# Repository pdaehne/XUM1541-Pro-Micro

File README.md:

# XUM1541 Pro Micro

The XUM1541 allows to connect devices that use the Commodore serial bus (IEC
bus) to modern computers via USB. You usually use it to create images of old
1541 or 1571 floppy disks by using a software called
[OpenCBM](https://github.com/OpenCBM/OpenCBM).

## Acknowlegements

This device is a clone of the
[ZoomFloppy](https://www.go4retro.com/products/zoomfloppy/) device developed by
Nate Lawson. It does not have the IEEE-488 interface, but apart from that it has
the same circuit as documented in the file
[zoomfloppy-schem-20100704.png](https://github.com/OpenCBM/OpenCBM/blob/master/xum1541/zoomfloppy-schem-20100704.png)
in the OpenCBM repository.

The idea for the "Activity" LED was taken from the
[XUM1541-II](https://github.com/tebl/C64-XUM1541-II) device designed by tebl.

## Ordering the PCB

The subdirectory "gerber-files" contains a Zip file you can use to order the PCB
from PCB manufacturers like PCBWay or JLCPCB. Simply upload the Zip on their web
page. When you plan to use the parallel port option, you have to order a PCB
that has the default thickness of 1.6mm, and I recommend to order a surface
finish of ENIG with gold fingers and chamfered edges, because it is much more
durable than the default HASL finish.

## Building the Adapter

### Bill of Materials

* __1x Pro Micro ATmega32U4 5V 16MHz Board__.

  There are two variants of this board, a 5V variant with 16MHz clock
  frequency, and a 3V variant with 8MHz. Make sure that you get the 5V variant!
  Also make sure that you get a Pro Micro Board based on the ATmega32U4. There
  are Pro Micro Boards available based on the Raspberry Pi Pico, these do not
  work!

  These boards come in at least three different widths. This XUM1541 PCB is
  designed to support all three widths (the distance between the two rows of
  pins can be either 15.24mm, 17.78mm or 20.32mm).

* __2x 1x12 Pin Headers Through Hole Straight 2.54mm pitch__

  These go onto the Pro Micro board. They should be included with the Pro Micro
  board.

* (Optional) __2x 2x12 Pin Sockets Through Hole Straight 2.54mm pitch__.

  These are used to connect the Pro Micro Board to the XUM1541 PCB. They are
  optional, you can solder the Pro Micro directly to the PCB instead.

* __1x 6 Pin DIN Socket Right Angle PCB mount__.

  The footprint is for Lumberg 010599 06 or equivalent sockets.

* (Optional) __1x 74LS06 Hex Inverter Buffers DIL-14__ (U1).

  Using this buffer chip is strongly recommended, especially when your're
  daisychaining more than one device on the IEC bus, but it is optional. When
  you install it, you should also install the capacitor C1 and the resistor
  network RN2. When you do not install it, you have to close the corresponding
  5 solder jumpers on the bottom of the XUM1541 PCB.

* (Optional) __1x IC Socket DIL-14__ (U1).

  Socket for the 74LS06. It is optional, you can alternatively solder the IC
  directly onto the XUM1541 PCB.

* (Optional) __1x Ceramic Capacitor 100nF 2.5mm pitch__ (C1).

  This is the blocking capacitor for U1. It is optional, you only need to
  install it when you install the 74LS06.

* (Optional) __1x Resistor Network 5x100kOhm SIL-6 Star Connection__ (RN2).

  This resistor network is only needed when installing the 74LS06. It pulls the
  inputs of the 74LS06 to ground.

  Warning: Please make sure that you get the right kind of resistor network.
  This network consists of 5 resistors which share one common connection on one
  side, i.e. there are 5 + 1 = 6 pins.

* (Optional) __1x Resistor Network 5x4.7kOhm SIL-10 Single Resistors__ (RN1).

  This resistor network is not used when you do not install the 74LS06.
  
  When you do install the 74LS06, you may optionally install this resistor
  network to limit the amount of current on the IEC bus. When you install the
  74LS06 and decide to leave this resistor network unpopulated, you have to
  close the corresponding 5 solder jumpers on the bottom of the XUM1541 PCB.

  Warning: Please make sure that you get the right kind of resistor network.
  This network consists of 5 resistors which all have their own separate two
  connections, i.e. there are 5 x 2 = 10 pins.

* (Optional) __1x Push Button 6x6mm__ (SW1).

  A reset switch that resets the Pro Micro, i.e. puts it into bootloader mode
  for 8 seconds. Completely optional, but having this switch makes installing
  a new firmware much more simple.

* (Optional) __2x LEDs 3mm or 5mm__ (D1 and D2).

  These are the power and activity LEDs. You can use any color you want, e.g.
  red for power and green for activity. These LEDs are optional, there are
  already corresponding LEDs on the Pro Micro board. When you install them, you
  also have to install matching series resistors R1 and R2. The activity LED
  requires an installed 74LS06!

* (Optional) __2x Resistors size 0207__ (R1 and R2).

  These are the series resistors for the LEDs D1 and D2. Of course they are only
  required when you actually install these LEDs! Their value depends on the
  types of LEDs you use (color) as well as the brightness you want to get. I
  recommend that you use a breadboard and check which values are ok for you.

* (Optional) __1x 1x3 Pin Headers Through Hole Straight 2.54mm pitch__

  This is a header for a serial TTL connection to the ATmega. This is only
  needed when you want to debug the XUM1541 firmware running on the
  microcontroller. You will probably not need this header. When you use it,
  keep in mind that it uses two pins also used by the parallel port of the
  XUM1541, so you will not be able to use both simultaneously.

### Soldering the Pin Headers to the Pro Micro Board

The first step is to solder the two 1x12 pin headers to the Pro Micro board.
I recommend to use a breadboard to make sure that the pin headers are correctly
aligned. But be careful not to drop solder onto the breadboard!

### Soldering the Socket for U1 (74LS06), the Capacitor C1 and the Resistor Networks RN2 and RN1

There are three options for building the XUM1541:

1. The simple version without U1, C1, RN2 and RN1. I generally do not recommend
   this option. You should only connect one single device to the IEC bus when
   using this option. You have to close the five solder jumpers below the U1
   footprint on the bottom of the PCB, and that is all.

2. The version with U1, C1 and RN2, but without RN1. The 74LS06 on U1 is a
   buffer chip, i.e. it is used to amplify the signals of the Pro Micro and to
   protect the ports of the Pro Micro. It is strongly recommended to install U1
   when you plan to connect more than one device to the IEC bus. RN2 are
   pull-down resistors to force the inputs of U1 to GND level when not driven by
   the Pro Micro.

   You can either install a DIL-14 socket for U1, or you can directly solder the
   74LS06 IC to the XUM1541 PCB. I personally prefer to use sockets. Make sure
   that the little notch of the socket points to the direction marked on the
   silk screen (to the right on the photo below).

   I recommend to wait until you are finished with soldering before you install
   the 74LS06 into the socket. Again make sure that the notch of the IC points
   to the direction of the notch of the socket (to the right on the photo).

   Now you have to install the blocking capacitor C1 next to U1.

   And you have to install the resistor network RN2 next to U1. Be careful, the
   orientation of this resistor network matters! There is a small dot on the
   resistor network that marks pin 1. Pin 1 is also marked on the silk screen
   of the PCB (left on the picture below).

   Because you are not installing resistor network RN1, you have to close five
   solder jumpers on the bottom of the PCB.

3. The full version with U1, C1, RN2 and RN1. This is the recommended version.
   RN1 limits the current between the IEC bus and the Pro Micro and protects the
   ports of the Pro Micro as well as your valuable retro devices connected to
   the IEC bus. The electric circuit is exactly the same as used for the
   [ZoomFloppy](https://www.go4retro.com/products/zoomfloppy/) available for
   purchase from Retro Innovations.

   Additionally to installing U1, C1 and RN2 (see documentation for variant 2
   above), you have to install resistor network RN1. Unlike resistor network
   RN2, the orientation of the network does not matter, but it is nevertheless
   good practice to solder pin 1 with the dot into the hole marked on the silk
   screen (at the top in the picture below).

### Soldering the Pin Sockets for the Pro Micro Board

This step is completely optional. You can solder the Pro Micro board directly
onto the XUM1541 PCB, but I prefer to install Pin Sockets.

There are two rows of through-holes on the PCB for each side of the Pro Micro
board. Each pair of rows has the same electrical connections, so you can freely
choose which one to use to adjust to different widths of the Pro Micro. When
the distance of the two rows of pins of your Pro Micro is 15.24mm, use the two
inner rows. When the distance is 20.32mm, use the two outer rows. When the
distance is 17.78mm, you use the outer row on one side, and the inner row on the
other side.

To solder the pin sockets straight, I recommend to stick them onto the pin
headers of the Pro Micro and put them onto the PCB. But again, be careful not
to drop solder onto the Pro Micro!

### Soldering the 6 Pin DIN socket

Now solder the 6 pin DIN socket onto the XUM1541 PCB. This is a straightforward
task.

### Soldering the Debug Header

The 1x3 pin header for debugging is optional. It provides a serial interface
with TTL levels and might be helpful when you are making changes to the firmware
of the Pro Micro, because you can use a serial terminal on another computer to
receive debug output from the Pro Micro.

### Soldering the LEDs and their series resistors

The LEDs for activity and power as well as their respective series resistors are
also optional. There are already corresponding LEDs on the Pro Micro board. I
intentionally do not give any values for the resistors here, because they depend
on the type of LED (color) you use as well as the level of brightness you want
to get. I recommend that you test different resistor values on a breadboard to
determine the right resistor values.

Important: The activity LED requires U1 to be installed!

When soldering the LEDs, keep in mind that the orientation of the LED matters.
There is a side of the LEDs that is flattened. This side is also marked on the
silk screen (the side facing away from the resistors). Unfortunately, this might
be little bit hard to see. Another hint is the length of the LED leads - the
long lead is the anode (+) and goes to the resistors, the short lead is the
cathode (-) and must point away from the resistors.

### Soldering the Reset Button

The reset button SW1 is optional. Pressing the reset button switches the Pro
Micro into boot loader mode for 8 seconds. Having a dedicated reset switch makes
installing a new firmware on the ATmega32U4 much simpler.

## Installing the Firmware

After soldering the XUM1541, you have to install the firmware onto the
Pro Micro. You will find the precompiled firmware in the
[OpenCBM GitHub repository](https://github.com/OpenCBM/OpenCBM/tree/master/xum1541).
Make sure that you fetch the correct firmware:

* When you did not install U1 (74LS06), you have to install the firmware
  "xum1541-PROMICRO-v??.hex", where "??" is the version number.

* When you did install U1, you have to install the firmware
  "xum1541-PROMICRO_7406-v??.hex".

There are many different ways to install the firmware. You can use an Atmel ICSP
programmer (or another Arduino), or you can install the firmware via the USB
port. The Pro Micro usually comes with the Arduino Leonardo boot loader
pre-installed. You switch the Pro Micro into boot loader mode by pressing the
reset button. When you did not install the reset button, you have to short the
RST pin of the Pro Micro board to GND. The Pro Micro stays in boot loader mode
for only 8 seconds, so you have to be quick now! I used a software called
"[avrdude](https://github.com/avrdudes/avrdude)" to install the firmware.
avrdude is also used by the Arduino IDE, so a simple way to get avrdude is to
install the Arduino IDE. I used the following command line to install the
firmware:

```
avrdude -v -patmega32u4 -cavr109 "-P/dev/tty.usbmodem2101" -b57600 -D "-Uflash:w:xum1541-PROMICRO_7406-v08.hex:i"
```

Of course you have to adjust the command line, especially the serial port!

## Installing OpenCBM

For installing OpenCBM, I recommend to have a look into the official
"[OpenCBM Users Guide](https://opencbm.trikaliotis.net/)" for more
information.

## Using a Parallel Cable

When you have a 1541 with a parallel cable, you can use that cable to achieve
much higher transfer rates. Simply connect the userport connector that you
usually connect to your C64 to the "Userport" at the side of the XUM1541. You
do not need to install any special kernal in your floppy - OpenCBM automatically
detects the presence of the cable and installs all necessary software on the
floppy. It should work out of the box.

When do not yet have a parallel cable, you might be interested in the following
of my projects:

https://github.com/pdaehne/C64-Parallel-Floppy-Cable

## License

XUM1541 Pro Micro (c) by Patrick Dähne

XUM1541 Pro Micro is licensed under a
Creative Commons Attribution-NonCommercial-ShareAlike 4.0 International License.

You should have received a copy of the license along with this
work. If not, see <https://creativecommons.org/licenses/by-nc-sa/4.0/>.

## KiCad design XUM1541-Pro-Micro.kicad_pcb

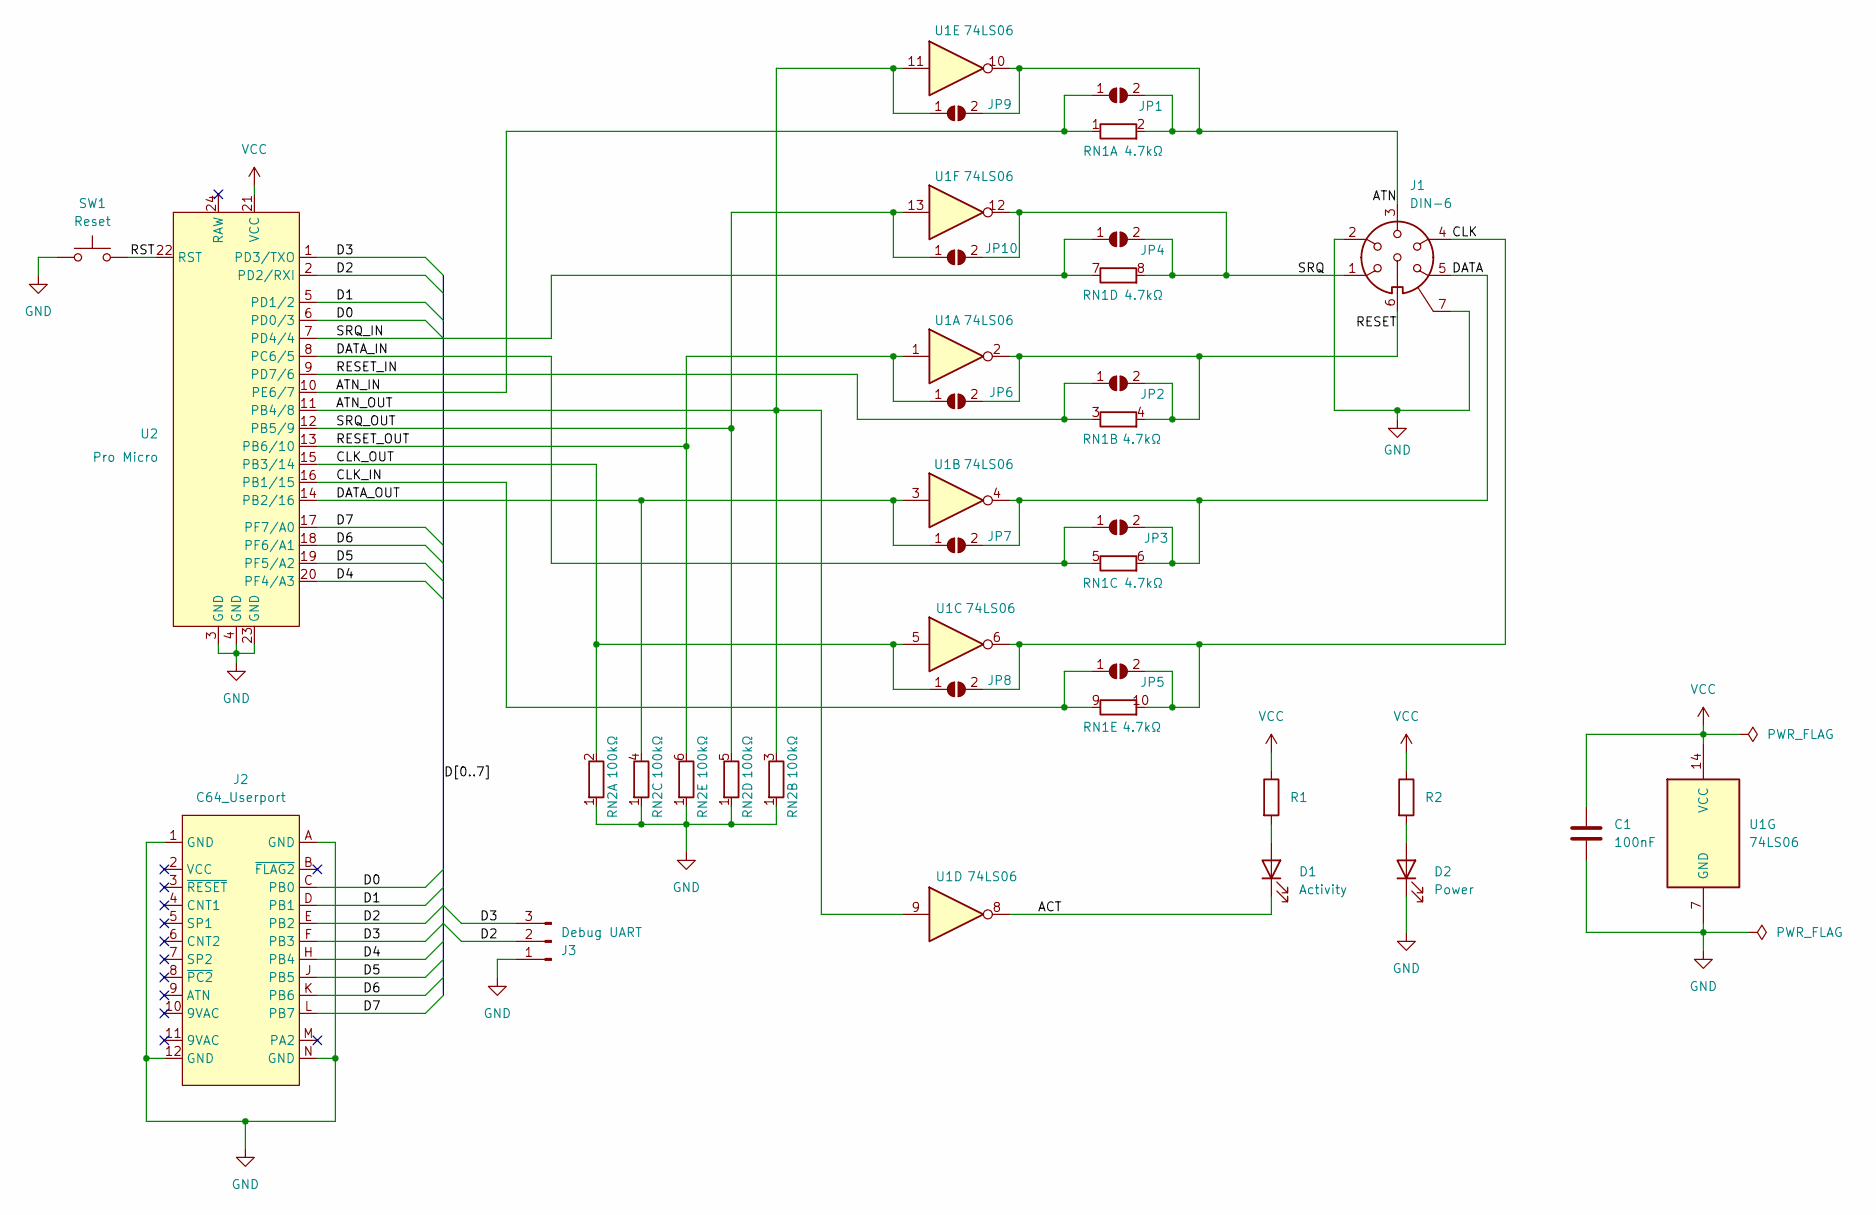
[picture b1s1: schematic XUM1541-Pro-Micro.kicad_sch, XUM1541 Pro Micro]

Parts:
C1: 100nF; C_Disc_D3.0mm_W1.6mm_P2.50mm
D1: Activity; LED_D3.0mm
D2: Power; LED_D3.0mm
J1: DIN-6
J2: C64_Userport; C64_Userport_Edge
J3: Debug UART; PinHeader_1x03_P2.54mm_Vertical
JP1, JP2, JP3, JP4, JP5, JP6, JP7, JP8, JP9, JP10: SolderJumper_2_Open; SolderJumper-2_P1.3mm_Open_RoundedPad1.0x1.5mm
R1, R2: R; R_Axial_DIN0207_L6.3mm_D2.5mm_P10.16mm_Horizontal
RN1: 4.7kΩ; R_Array_SIP10
RN2: 100kΩ; R_Array_SIP6
SW1: Reset; SW_PUSH_6mm
U1: 74LS06; DIP-14_W7.62mm_Socket_LongPads
U2: Pro Micro; Pro_Micro

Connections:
/ACT: D1.1 (K), U1.8
/ATN: J1.3, JP1.2 (B), JP9.2 (B), RN1.2 (R1.2), U1.10
/ATN_IN: JP1.1 (A), RN1.1 (R1.1), U2.10 (PE6/7)
/ATN_OUT: JP9.1 (A), RN2.3 (R2.2), U1.9, U1.11, U2.11 (PB4/8)
/CLK: J1.4, JP5.2 (B), JP8.2 (B), RN1.10 (R5.2), U1.6
/CLK_IN: JP5.1 (A), RN1.9 (R5.1), U2.16 (PB1/15)
/CLK_OUT: JP8.1 (A), RN2.2 (R1.2), U1.5, U2.15 (PB3/14)
/D0: J2.C (PB0), U2.6 (PD0/3)
/D1: J2.D (PB1), U2.5 (PD1/2)
/D2: J2.E (PB2), J3.2, U2.2 (PD2/RXI)
/D3: J2.F (PB3), J3.3, U2.1 (PD3/TXO)
/D4: J2.H (PB4), U2.20 (PF4/A3)
/D5: J2.J (PB5), U2.19 (PF5/A2)
/D6: J2.K (PB6), U2.18 (PF6/A1)
/D7: J2.L (PB7), U2.17 (PF7/A0)
/DATA: J1.5, JP3.2 (B), JP7.2 (B), RN1.6 (R3.2), U1.4
/DATA_IN: JP3.1 (A), RN1.5 (R3.1), U2.8 (PC6/5)
/DATA_OUT: JP7.1 (A), RN2.4 (R3.2), U1.3, U2.14 (PB2/16)
/RESET: J1.6, JP2.2 (B), JP6.2 (B), RN1.4 (R2.2), U1.2
/RESET_IN: JP2.1 (A), RN1.3 (R2.1), U2.9 (PD7/6)
/RESET_OUT: JP6.1 (A), RN2.6 (R5.2), U1.1, U2.13 (PB6/10)
/RST: SW1.2, U2.22 (RST)
/SRQ: J1.1, JP4.2 (B), JP10.2 (B), RN1.8 (R4.2), U1.12
/SRQ_IN: JP4.1 (A), RN1.7 (R4.1), U2.7 (PD4/4)
/SRQ_OUT: JP10.1 (A), RN2.5 (R4.2), U1.13, U2.12 (PB5/9)
GND: C1.2, D2.1 (K), J1.2, J1.7, J2.1 (GND), J2.12 (GND), J2.A (GND), J2.N (GND), J3.1, RN2.1 (R1), SW1.1, U1.7 (GND), U2.3 (GND), U2.4 (GND), U2.23 (GND)
unnamed: D1.2 (A), R1.2
unnamed: D2.2 (A), R2.2
VCC: C1.1, R1.1, R2.1, U1.14 (VCC), U2.21 (VCC)

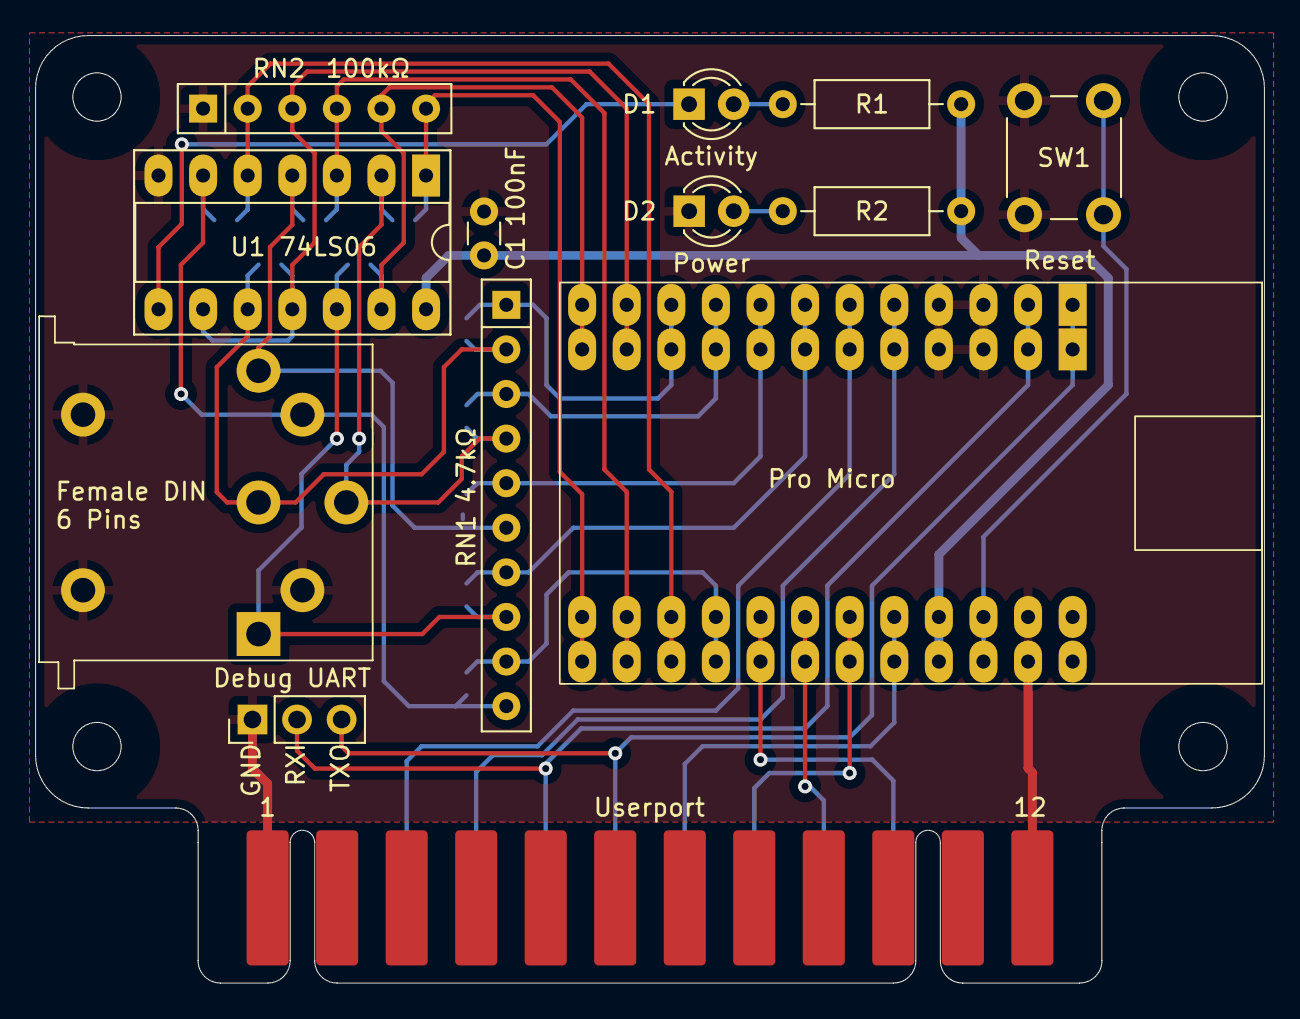
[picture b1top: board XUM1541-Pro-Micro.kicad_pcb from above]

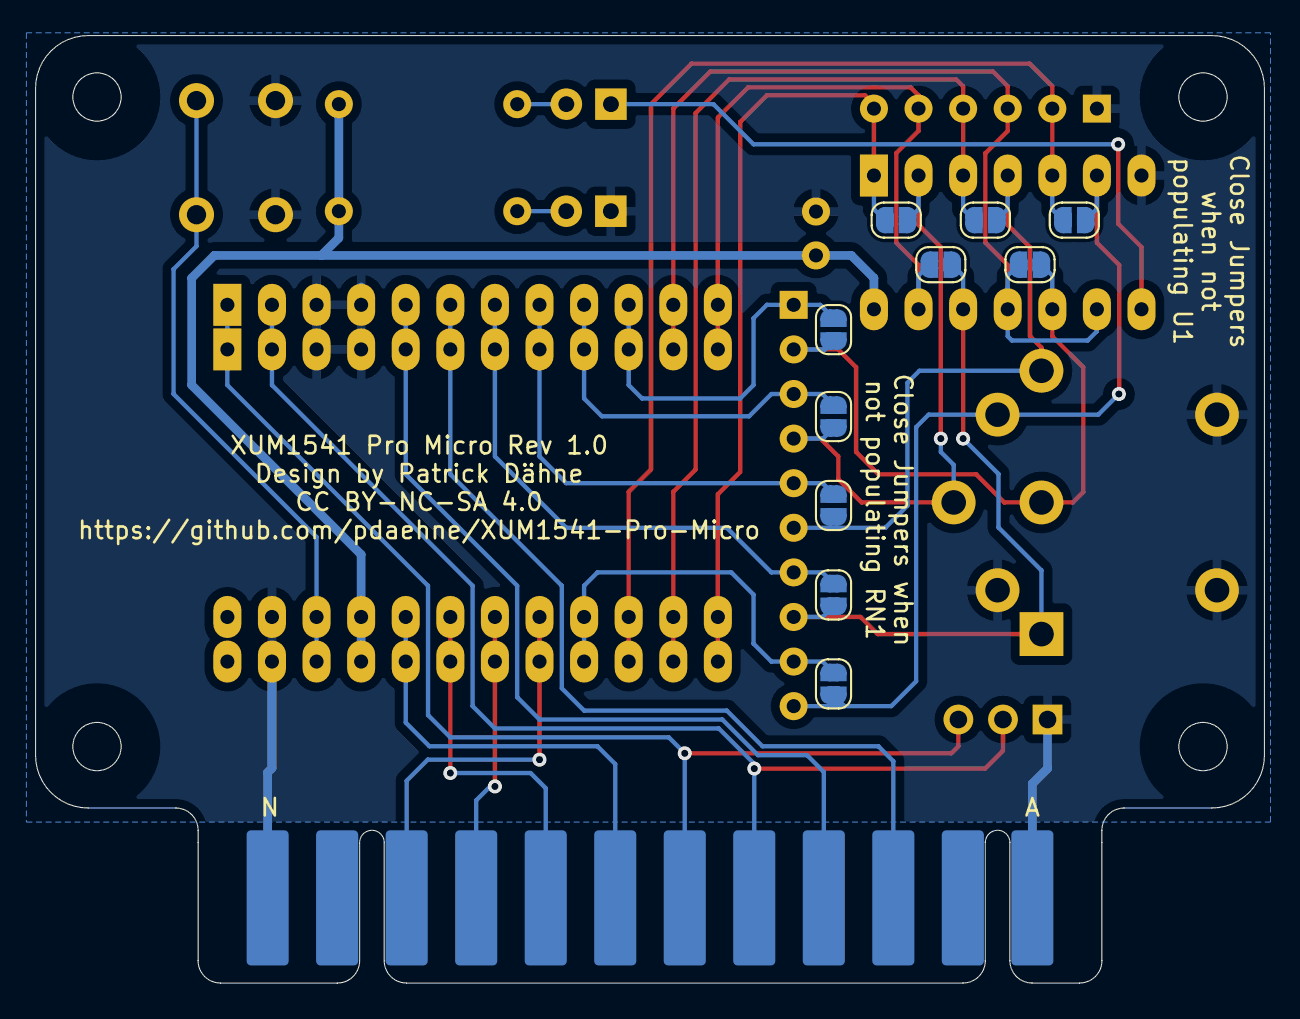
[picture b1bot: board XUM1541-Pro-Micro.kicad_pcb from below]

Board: 2 copper layers, 70.0 x 54.0 mm, 23 parts (10 on the bottom side), 29 nets.

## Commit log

2024-09-13 Initial check-in
2024-09-16 Schematic cleanup
2025-01-20 Fixed access rights
2025-12-02 Fixed some typos
2025-12-05 Added clarification about the resistor networks
2025-12-05 Added Acknowledgements
2025-12-15 Added information about using parallel cables
2025-12-17 Added reference to parallel cable project

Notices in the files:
XUM1541-Pro-Micro.kicad_pcb:
Patrick Dähne CC BY-NC-SA 4.0
CC BY-NC-SA 4.0
